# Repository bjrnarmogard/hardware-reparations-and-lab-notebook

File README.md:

# 🛠️ Sony Headphone Cable Repair (Litz Wire & Soldering Techniques)

This project documents the practical troubleshooting and successful repair of a pair of Sony headphones where the cable to one of the ear cups had snapped. The project serves as a practical self-study in handling ultra-fine enameled conductors and maintaining thermal control under challenging laboratory conditions.

## 🔧 Tools Used in the Lab
* **Soldering Iron:** Biltema (standard unregulated soldering iron) with spring stand
* **Fixing & Positioning:** "Helping Hand" with alligator clips and a fine mechanical probe
* **Consumables:** Standard soldering tin and electrical insulation tape

## 💡 Inspiration and Lessons Learned
* **Inspiration:** This repair was inspired by mechanics channels on YouTube, specifically `@LyThiXien-886` (formerly Ly Ly Mechanical), which demonstrate advanced troubleshooting and mechanical repairs of damaged wiring harnesses using basic tools.
* **Lab Experience:** Because the wire leads were extremely short and the circuit lacked external strain relief during the joining process, keeping everything stable was a significant challenge. This resulted in a few classic finger burns along the way, but provided valuable experience regarding the importance of proper fixation and patience in fine mechanical work.

## 🔍 Troubleshooting Methodology & Technical Challenges
1. **Verifying the Fault Location:** Troubleshooting was initially attempted with a digital multimeter, but due to the thin insulation lacquer on the conductors, it did not provide a reliable reading. The break location and signal path were subsequently identified by performing a mechanical compression test (squeezing the leads together) during continuous audio playback until stable, uninterrupted two-way audio was verified.
2. **Oxidation and Enamel Removal:** The red signal conductor was coated with a colored enamel lacquer that prevented the solder from adhering (poor wetting). Using a basic soldering iron increased the risk of rapid oxidation on the tip, causing the tin to bead up and roll off.
3. **Thermo-Mechanical Soldering Technique:** To overcome this, the soldering iron was placed underneath the joint for maximum heat transfer (burning off the enamel lacquer), while the fine mechanical tool was used from above to pinch the conductors stably together at the exact moment of melting. This overcame the oxidation, stripped the remaining lacquer, and ensured immediate adhesion.
4. **Insulation:** The joint was immediately insulated with tape after a successful function test to act as a temporary strain relief and prevent short circuits during future use.

## 📸 Images from the Process

### Product Overview

### Detail of the Soldered and Taped Cable Joint

### Tools and Equipment Used on the Workbench

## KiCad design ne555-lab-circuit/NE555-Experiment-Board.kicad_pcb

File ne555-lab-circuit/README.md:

# NE555 Lab Circuit - Resistance Measurement Setup

This project documents the schematic design, simulation, and hardware layout of a laboratory experiment circuit based on the classic NE555 timer integrated circuit. The design translates concepts from text to a production-ready hardware prototype.

## Reference & Inspiration
- **Source:** *Practical Electronics* Magazine, **September 2026** issue.
- **Section:** *Circuit Surgery* – "Measuring resistance with a 555 timer chip".
- **Implementation:** The LTspice simulation parameters follow the magazine's methodology for verifying stable oscillation and signal behavior. The subsequent KiCad schematic capture, custom footprint assignment for laboratory hand-soldering, and 3D PCB layout verification were performed independently as standalone hardware development.

## Technical Summary
- **Circuit Architecture:** Configured as an astable multivibrator (oscillator) designed to output a stable square wave where frequency variations can be used to determine resistance parameters.
- **Signal Integrity:** Includes local 0.1µF decoupling capacitors placed closely to the VCC/GND pins of the ICs to suppress switching noise and stabilize the internal comparator thresholds.
- **PCB Design:** Developed in KiCad using Through-Hole Technology (THT) footprints (DIP-8 for the NE555P) to ensure high thermal tolerance during assembly with unregulated soldering irons. Traces are routed using clean 45-degree angles to optimize copper geometry and maintain manufacturing rule compliance. 
- **Testing Interface:** Dedicated 1-pin headers are integrated directly at the output pins (OUT) to serve as physical test points for secure oscilloscope probing.

## Tools Used
- **LTspice:** Analog circuit simulation and waveform verification.
- **KiCad EDA:** Schematic capture, trace routing, and 3D visualization.

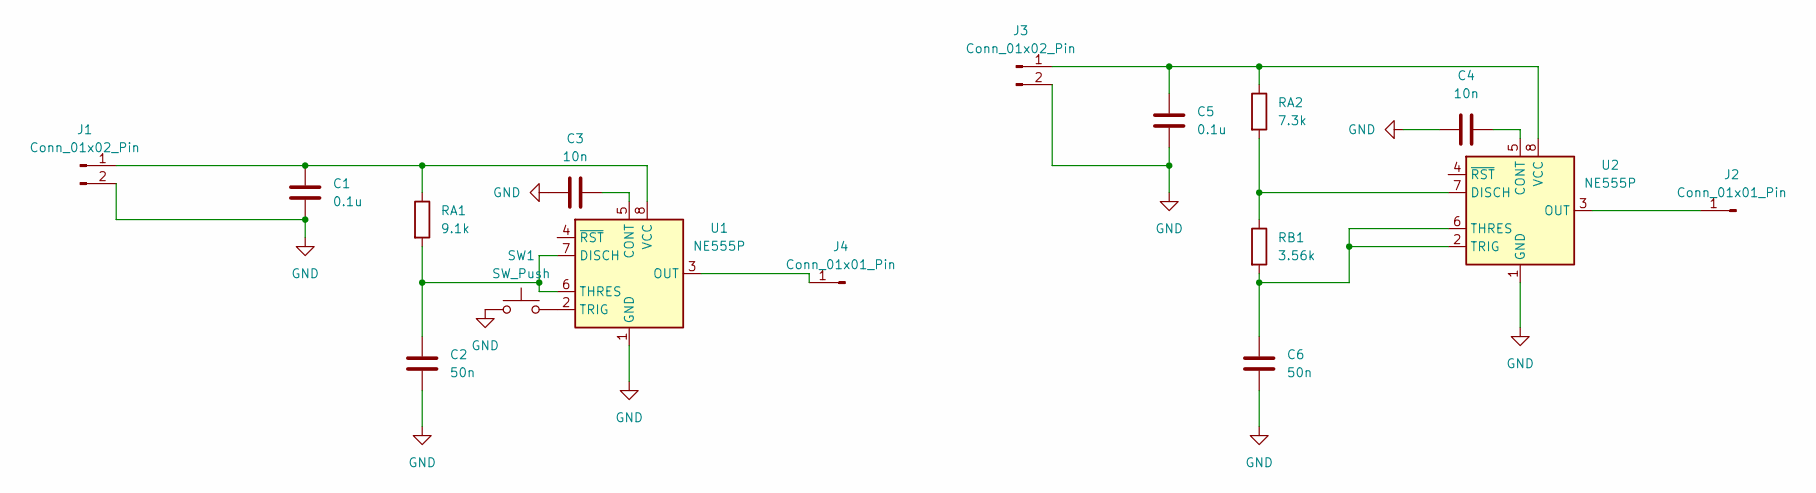
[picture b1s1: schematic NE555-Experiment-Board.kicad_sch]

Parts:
C1, C5: 0.1u; C_Disc_D5.0mm_W2.5mm_P2.50mm
C2, C6: 50n; C_Disc_D5.0mm_W2.5mm_P2.50mm
C3, C4: 10n; C_Disc_D5.0mm_W2.5mm_P2.50mm
J1, J3: Conn_01x02_Pin; PinHeader_1x02_P2.54mm_Vertical
J2, J4: Conn_01x01_Pin; PinHeader_1x01_P2.54mm_Vertical
RA1: 9.1k; R_Axial_DIN0207_L6.3mm_D2.5mm_P7.62mm_Horizontal
RA2: 7.3k; R_Axial_DIN0207_L6.3mm_D2.5mm_P7.62mm_Horizontal
RB1: 3.56k; R_Axial_DIN0207_L6.3mm_D2.5mm_P7.62mm_Horizontal
SW1: SW_Push; SW_PUSH_6mm
U1, U2: NE555P; DIP-8_W7.62mm

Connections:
GND: C1.2, C2.2, C3.1, C4.1, C5.1, C6.2, J1.2, J3.2, SW1.1, U1.1 (GND), U2.1 (GND)
unnamed: C1.1, J1.1, RA1.1, U1.8 (VCC)
unnamed: J2.1 (Pin_1_1), U2.3 (OUT)
unnamed: C5.2, J3.1, RA2.1, U2.8 (VCC)
unnamed: J4.1 (Pin_1_1), U1.3 (OUT)
unnamed: C3.2, U1.5 (CONT)
unnamed: C2.1, RA1.2, U1.6 (THRES), U1.7 (DISCH)
unnamed: SW1.2, U1.2 (TRIG)
unnamed: C4.2, U2.5 (CONT)
unnamed: RA2.2, RB1.1, U2.7 (DISCH)
unnamed: C6.1, RB1.2, U2.2 (TRIG), U2.6 (THRES)

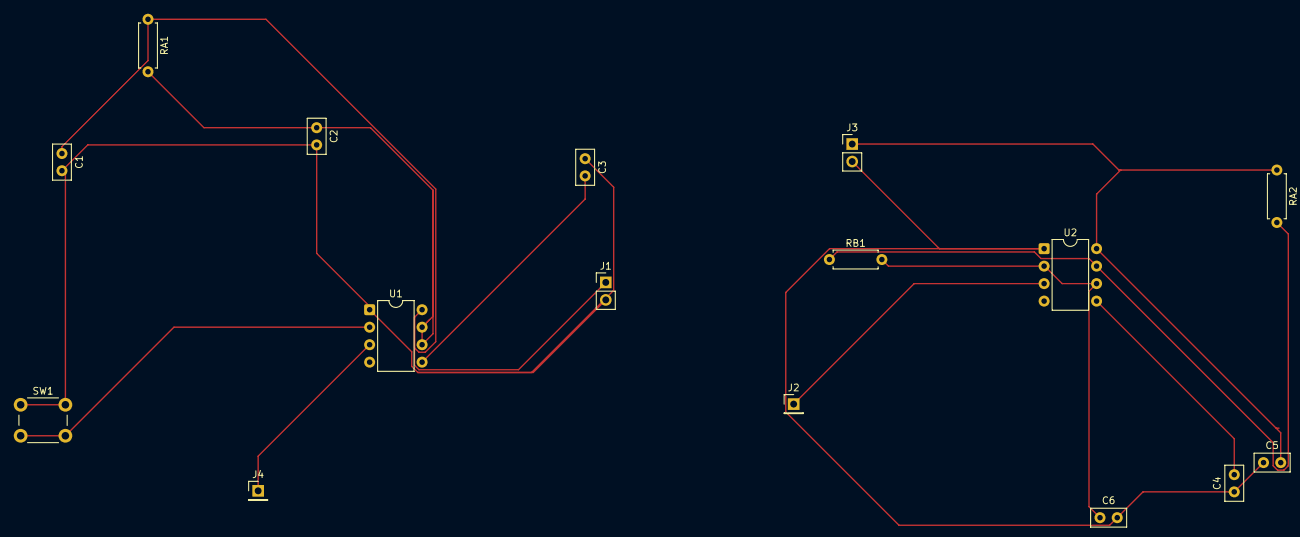
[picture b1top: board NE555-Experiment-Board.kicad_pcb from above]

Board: 2 copper layers, 16 parts (0 on the bottom side), 11 nets.
